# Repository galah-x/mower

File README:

Repository for files to upgrade a Ryobi RM480e ride on battery mower
from its original 4 75AH lead acid batteries
to Lithium Iron Phosphate (LFP) 100AH batteries
With a battery balance facility.

The 12V LFP batteries have internal battery balance, to balance the 4 cells each contains.
This repo is about balancing the 4 12V batteries to each other.

Discussion at https://hackaday.io/project/202788-ryobi-480e-mower-lfp-battery-upgrade-with-balance

Repo signifiant contents:

VMON is the per battery voltage monitor and balance board
vmon/vmn/vmn.ino    arduino code for an esp32
vmon/vmon/vmon.pdf  board schematic
vmon/vmon/gerbers/  board manufacturing info
vmon/vmon           kicad layout directory

IMON is the current monitor from a current shunt
imon/imon.ino       arduino code for an esp32
vmon/imon/imon.pdf  schematic
there is no imon layout, its hacked onto a vmon board as I discovered a design oversight in the
adc on the mco board near the runup phase. Too much of a hurry to mow the lawn to wait for a pcb to be made and shipped.

MCO is the Mower comms controller board. This is where the mower logic runs.
mcomms/mco/mco.ino     and other files in that directory is the arduino source for the mco board
mcomms/mcomms.pdf      board schematic
mcomms/mcomms          kicad layout files
mcomms/mcomms/gerbers  pcb manufacturing files

MMC is the mower charge controller. Really its a display board next to the power supply with a LCD and
rotary encoder. It displays each battery voltage and balance state, charger voltage, charge current, charge state, mower temperature.
mcharger_if/mcharge_if.pdf       schematic
mcharger_if/mcc/mcc.ino          arduino code, together with remainder of the directory
mcharger_if/mcharger_if/         kicad layout dir
mcharger_if/mcharger_if/gerbers  pcb manufacturing information

PSU is a wifi to serial converter used to allow mco to control and monitor the replacement charger, made from a 1200W 60V smps module and a DPM8624 remote programmable power supply.
vichyctl/psu/psu.ino        arduino code for psu
vichyctl/vichyctl.pdf       schematic for board
vichyctl/vichyctl/gerbers/  layout files
vichyctl/vichyctl           kicad layout directory.   Originally a board to permit remote Wifi access to a vichy VC8145 multimeter 

I didn't draw a charger schematic.
Connect the mains to the smps power supply.
Connect the 60V out of the SMPS to the input pins of the DPM8624
Connect the 4 pins on the PSU board (5V, 0V, TX, RX) to the matching 4 control pins on the DPM86224.
Connect the 2 output pins on the DPM8624 to a charger cable likely repurposed from your old charger
in the charger plug, add a wire to connect the middle sense pin to +48V, ie charger positive. 

mower_system_connect is a top level schematic of new stuff in the mower.
mower_system_connect/mower_system_connect.pdf

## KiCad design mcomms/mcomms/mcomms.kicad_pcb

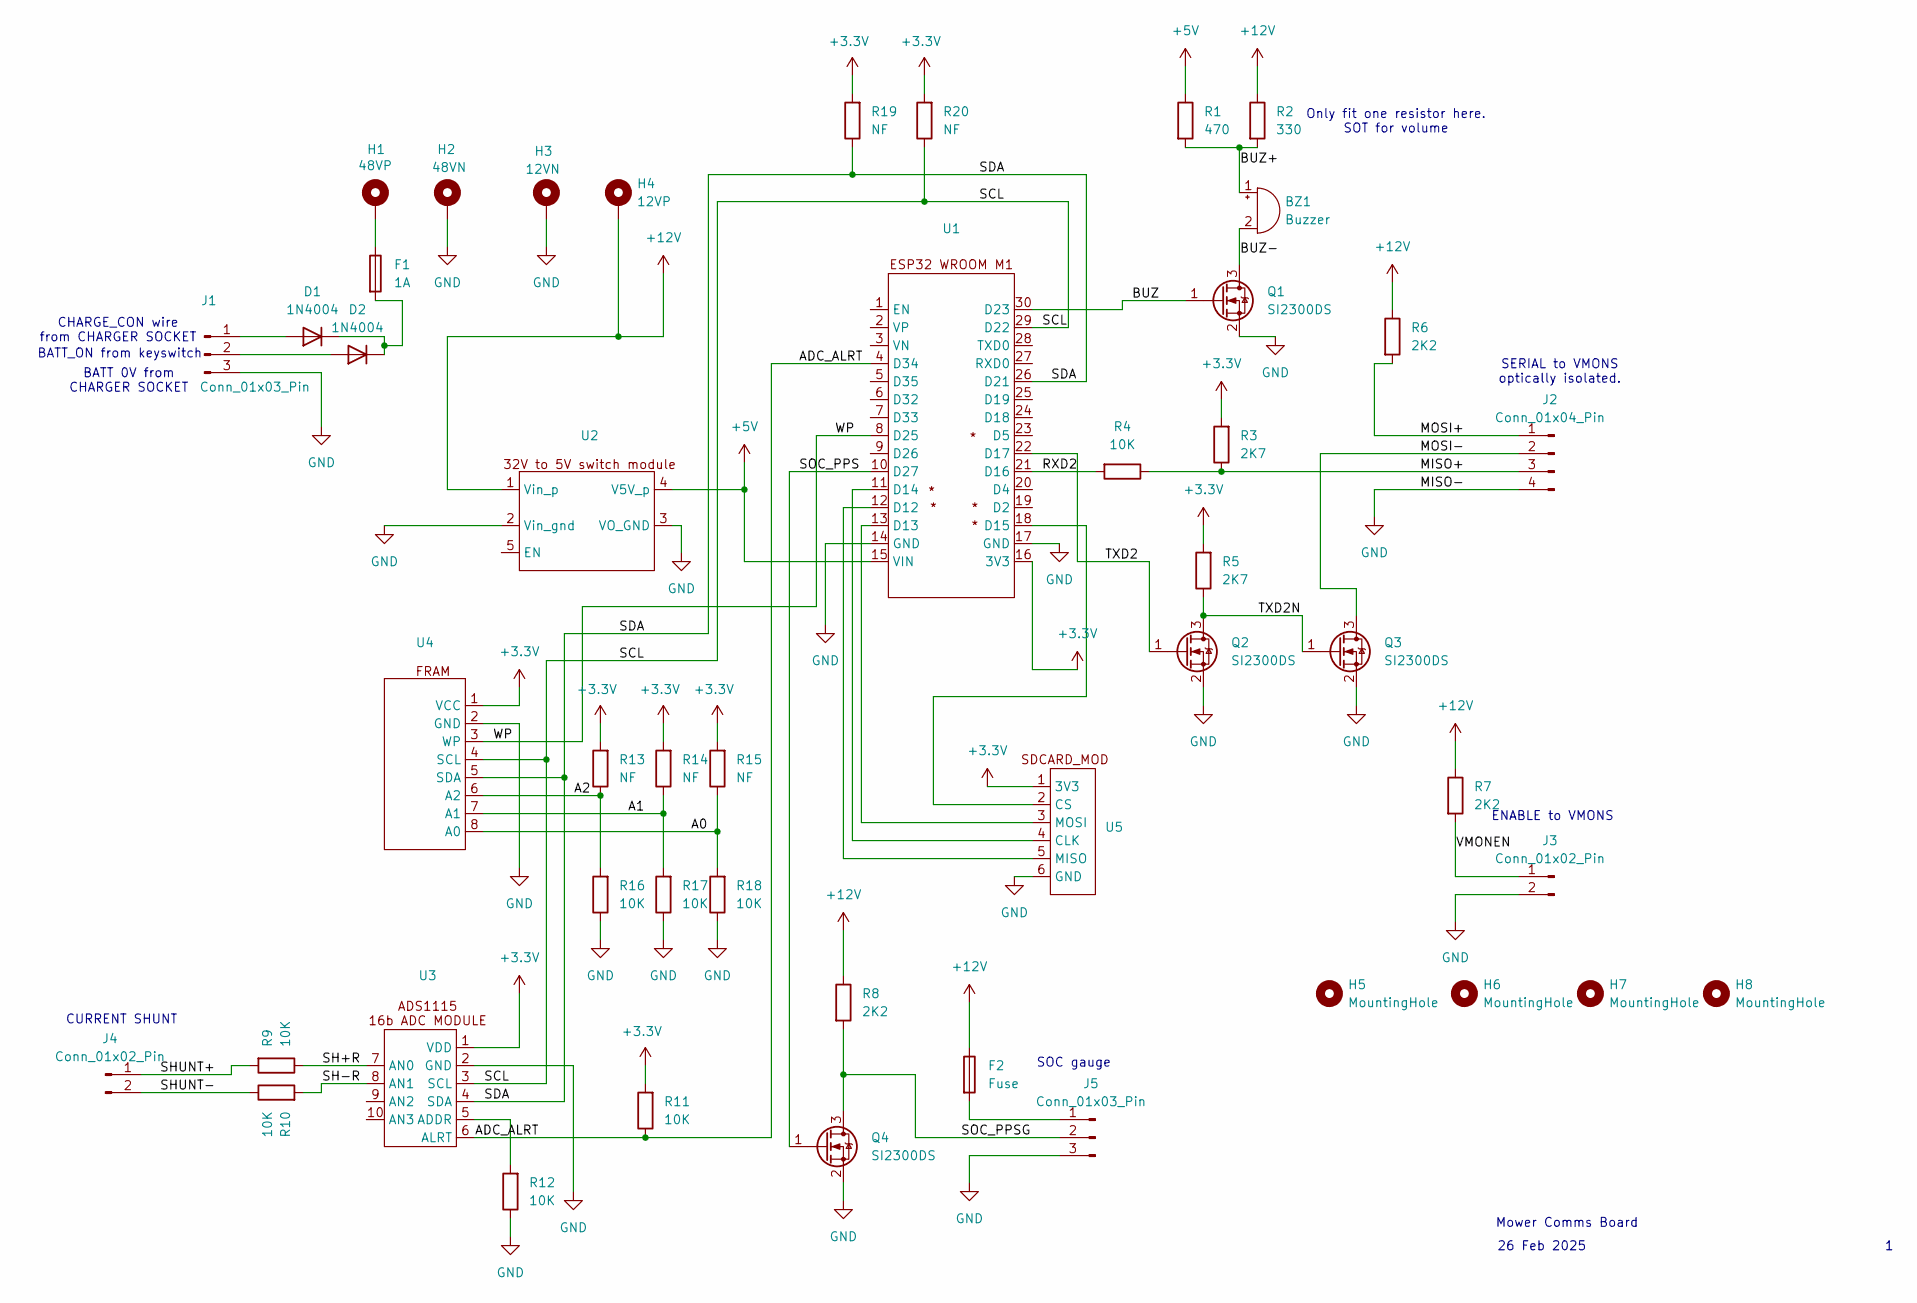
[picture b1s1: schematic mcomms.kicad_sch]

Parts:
BZ1: Buzzer; Buzzer_12x9.5RM7.6
D1, D2: 1N4004; D_A-405_P12.70mm_Horizontal
F1: 1A; Fuse_1206_3216Metric_Pad1.42x1.75mm_HandSolder
F2: Fuse; Fuse_1206_3216Metric_Pad1.42x1.75mm_HandSolder
H1: 48VP; MountingHole_2.2mm_M2_DIN965_Pad_TopBottom
H2: 48VN; MountingHole_2.2mm_M2_DIN965_Pad_TopBottom
H3: 12VN; MountingHole_2.2mm_M2_DIN965_Pad_TopBottom
H4: 12VP; MountingHole_2.2mm_M2_DIN965_Pad_TopBottom
H5, H6, H7, H8: MountingHole; MountingHole_3.2mm_M3_DIN965_Pad
J1, J5: Conn_01x03_Pin; PhoenixContact_MC_1,5_3-G-5.08_1x03_P5.08mm_Horizontal
J2: Conn_01x04_Pin; PhoenixContact_MC_1,5_4-G-5.08_1x04_P5.08mm_Horizontal
J3, J4: Conn_01x02_Pin; PhoenixContact_MC_1,5_2-G-5.08_1x02_P5.08mm_Horizontal
Q1, Q2, Q3, Q4: SI2300DS; SOT-23
R1: 470; R_Axial_DIN0309_L9.0mm_D3.2mm_P12.70mm_Horizontal
R2: 330; R_Axial_DIN0309_L9.0mm_D3.2mm_P12.70mm_Horizontal
R3, R5: 2K7; R_0805_2012Metric_Pad1.20x1.40mm_HandSolder
R4, R9, R10, R11, R12, R16, R17, R18: 10K; R_0805_2012Metric_Pad1.20x1.40mm_HandSolder
R6, R7, R8: 2K2; R_0805_2012Metric_Pad1.20x1.40mm_HandSolder
R13, R14, R15, R19, R20: NF; R_0805_2012Metric_Pad1.20x1.40mm_HandSolder
U1: ESP32_WROOM_M1
U2: switcher_en
U3: R_Array_SIP10
U4: SIP-8_19x3mm_P2.54mm
U5: R_Array_SIP6

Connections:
+3.3V: R3.2, R5.2, R11.2, R13.2, R14.2, R15.2, R19.2, R20.2, U1.16 (3V3), U3.1 (VDD), U4.1 (VCC), U5.1 (3V3)
+5V: R1.1, U1.15 (VIN), U2.4 (V5V_p)
+12V: F2.1, H4.1, R2.1, R6.1, R7.1, R8.1, U2.1 (Vin_p)
/A0: R15.1, R18.2, U4.8 (A0)
/A1: R14.1, R17.2, U4.7 (A1)
/A2: R13.1, R16.2, U4.6 (A2)
/ADC_ALRT: R11.1, U1.4 (D34), U3.6 (ALRT)
/BUZ: Q1.1 (G), U1.30 (D23)
/BUZ+: BZ1.1 (+), R1.2, R2.2
/BUZ-: BZ1.2 (-), Q1.3 (D)
/MISO+: J2.3, R3.1, R4.1
/MOSI+: J2.1, R6.2
/MOSI-: J2.2, Q3.3 (D)
/RXD2: R4.2, U1.21 (D16)
/SCL: R20.1, U1.29 (D22), U3.3 (SCL), U4.4 (SCL)
/SDA: R19.1, U1.26 (D21), U3.4 (SDA), U4.5 (SDA)
/SH+R: R9.1, U3.7 (AN0)
/SH-R: R10.2, U3.8 (AN1)
/SHUNT+: J4.1, R9.2
/SHUNT-: J4.2, R10.1
/SOC_PPS: Q4.1 (G), U1.10 (D27)
/SOC_PPSG: J5.2, Q4.3 (D), R8.2
/TXD2: Q2.1 (G), U1.22 (D17)
/TXD2N: Q2.3 (D), Q3.1 (G), R5.1
/VMONEN: J3.1, R7.2
/WP: U1.8 (D25), U4.3 (WP)
GND: H2.1, H3.1, J1.3, J2.4, J3.2, J5.3, Q1.2 (S), Q2.2 (S), Q3.2 (S), Q4.2 (S), R12.1, R16.1, R17.1, R18.1, U1.14 (GND), U1.17 (GND), U2.2 (Vin_gnd), U2.3 (VO_GND), U3.2 (GND), U4.2 (GND), U5.6 (GND)
unnamed: D1.2 (A), J1.1
unnamed: D1.1 (K), D2.1 (K), F1.2
unnamed: D2.2 (A), J1.2
unnamed: F1.1, H1.1
unnamed: F2.2, J5.1
unnamed: U1.12 (D12), U5.5 (MISO)
unnamed: U1.13 (D13), U5.3 (MOSI)
unnamed: U1.11 (D14), U5.4 (CLK)
unnamed: U1.18 (D15), U5.2 (CS)
unnamed: R12.2, U3.5 (ADDR)

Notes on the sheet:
SERIAL to VMONS optically isolated.
CHARGE_CON wire from CHARGER SOCKET
CURRENT SHUNT
ENABLE to VMONS
BATT_ON from keyswitch
Mower Comms Board
BATT 0V from CHARGER SOCKET
26 Feb 2025
SOC gauge
Only fit one resistor here. SOT for volume

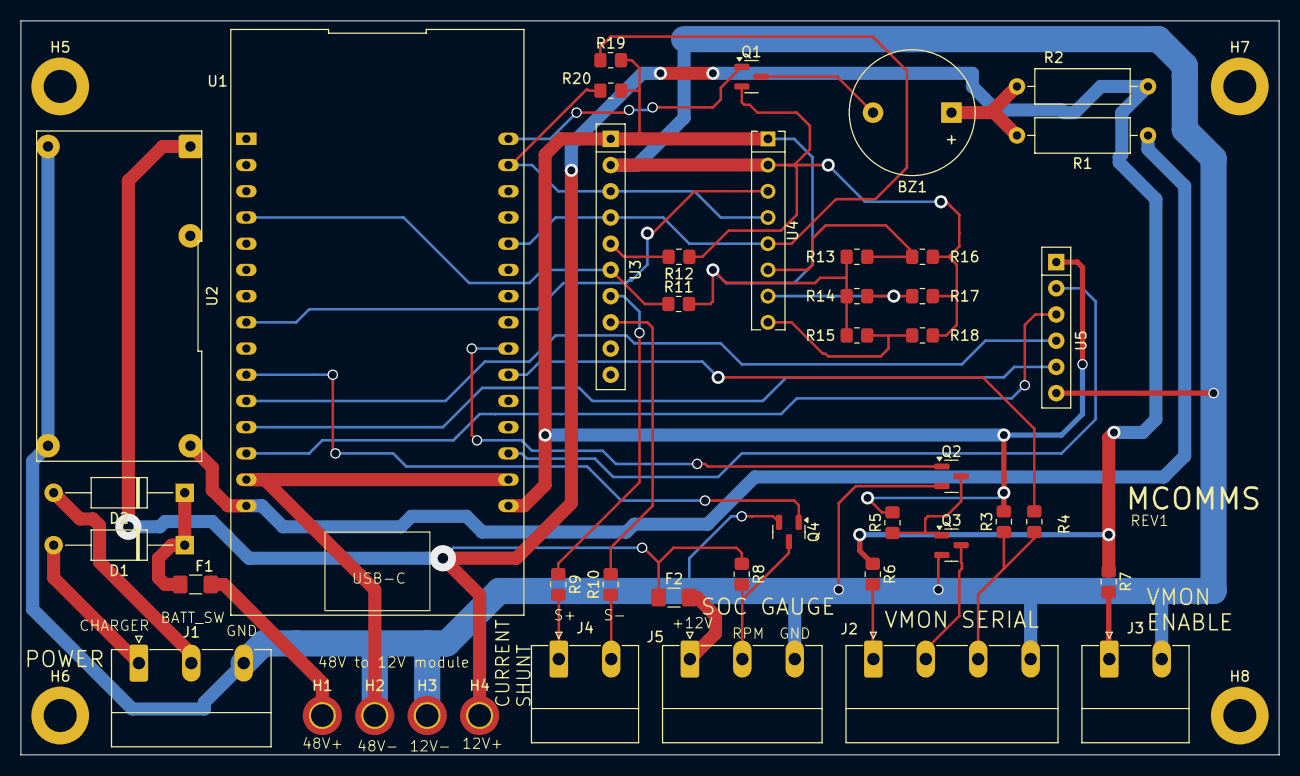
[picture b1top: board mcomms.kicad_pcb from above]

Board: 2 copper layers, 121.9 x 71.1 mm, 47 parts (0 on the bottom side), 37 nets.

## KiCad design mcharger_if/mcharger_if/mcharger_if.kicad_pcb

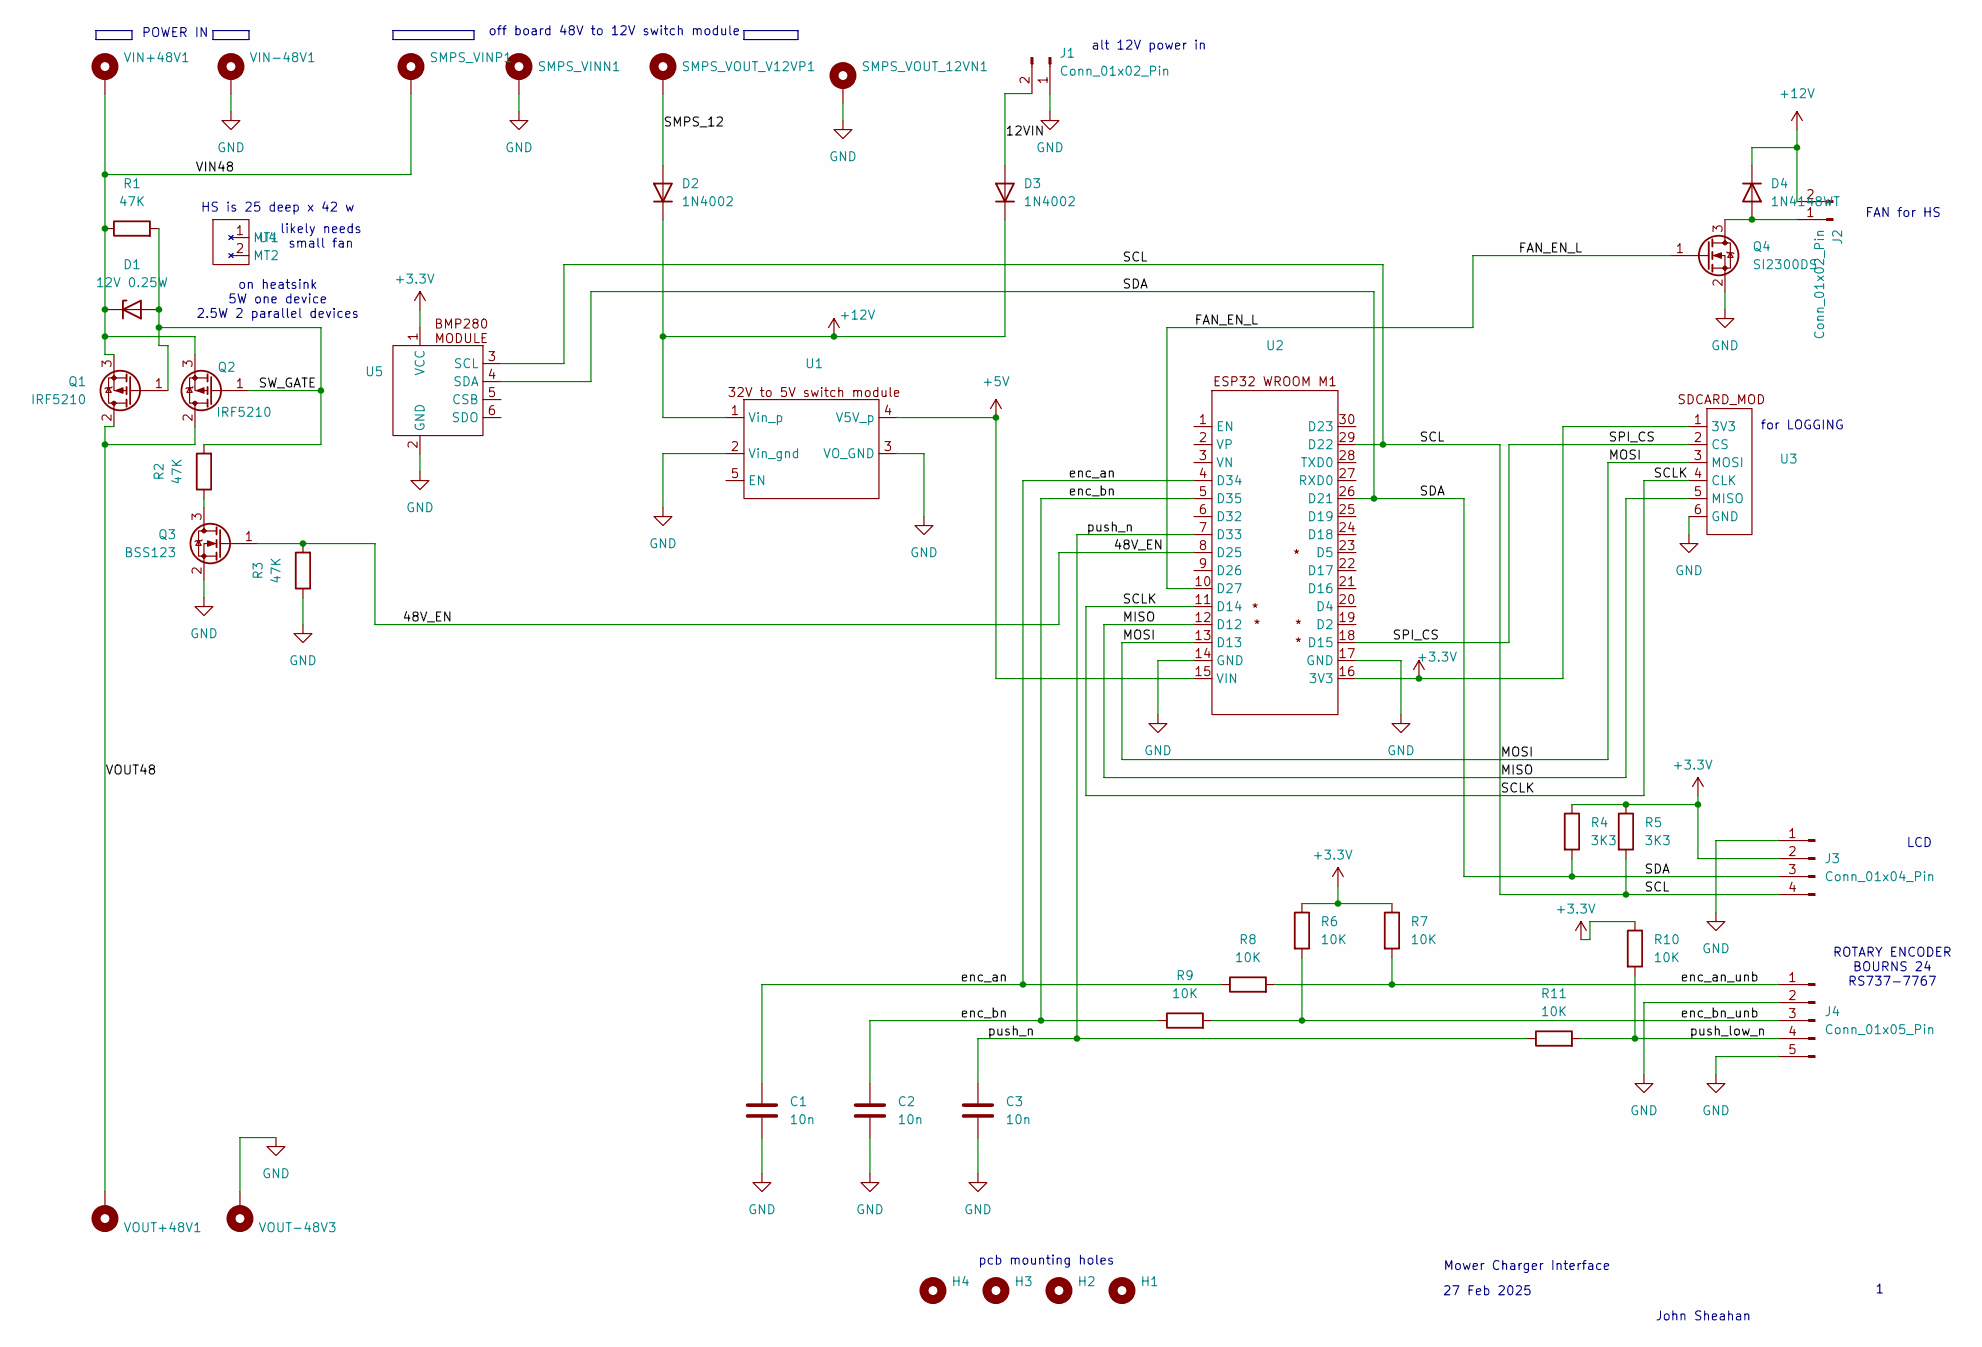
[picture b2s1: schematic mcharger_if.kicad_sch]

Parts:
C1, C2, C3: 10n; C_0603_1608Metric_Pad1.08x0.95mm_HandSolder
D1: 12V 0.25W; D_0805_2012Metric_Pad1.15x1.40mm_HandSolder
D2, D3: 1N4002; D_DO-41_SOD81_P10.16mm_Horizontal
D4: 1N4148WT; D_SOD-523
H1, H2, H3, H4: MountingHole; MountingHole_3.2mm_M3_DIN965
J1, J2: Conn_01x02_Pin; PhoenixContact_MC_1,5_2-G-5.08_1x02_P5.08mm_Horizontal
J3: Conn_01x04_Pin; JST_XH_B4B-XH-AM_1x04_P2.50mm_Vertical
J4: Conn_01x05_Pin; JST_XH_B5B-XH-A_1x05_P2.50mm_Vertical
Q1, Q2: IRF5210; TO-220-3_Vertical
Q3: BSS123; SOT-23
Q4: SI2300DS; SOT-23
R1, R2, R3: 47K; R_0805_2012Metric_Pad1.20x1.40mm_HandSolder
R4, R5: 3K3; R_0805_2012Metric_Pad1.20x1.40mm_HandSolder
R6, R7, R8, R9, R10, R11: 10K; R_0805_2012Metric_Pad1.20x1.40mm_HandSolder
SMPS_VINN1: MountingHole_Pad; MountingHole_2.2mm_M2_DIN965_Pad_TopBottom
SMPS_VINP1: MountingHole_Pad; MountingHole_2.2mm_M2_DIN965_Pad_TopBottom
SMPS_VOUT_12VN1: MountingHole_Pad; MountingHole_2.2mm_M2_DIN965_Pad_TopBottom
SMPS_VOUT_V12VP1: MountingHole_Pad; MountingHole_2.2mm_M2_DIN965_Pad_TopBottom
U1: switcher_en
U2: ESP32_WROOM_M1
U3, U5: R_Array_SIP6
U4: TO220_m1
VIN+48V1: MountingHole_Pad; MountingHole_3.2mm_M3_DIN965_Pad_TopBottom
VIN-48V1: MountingHole_Pad; MountingHole_3.2mm_M3_DIN965_Pad_TopBottom
VOUT+48V1: MountingHole_Pad; MountingHole_3.2mm_M3_DIN965_Pad_TopBottom
VOUT-48V3: MountingHole_Pad; MountingHole_3.2mm_M3_DIN965_Pad_TopBottom

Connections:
+3.3V: J3.2, R4.1, R5.1, R6.1, R7.1, R10.1, U2.16 (3V3), U3.1 (3V3), U5.1 (VCC)
+5V: U1.4 (V5V_p), U2.15 (VIN)
+12V: D2.1 (K), D3.1 (K), D4.1 (K), J2.2, U1.1 (Vin_p)
/12VIN: D3.2 (A), J1.2
/48V_EN: Q3.1 (G), R3.2, U2.8 (D25)
/FAN_EN_L: Q4.1 (G), U2.10 (D27)
/SDA: J3.3, R4.2, U2.26 (D21), U5.4 (SDA)
/SMPS_12: D2.2 (A), SMPS_VOUT_V12VP1.1
/SPI_CS: U2.18 (D15), U3.2 (CS)
/SW_GATE: D1.2 (A), Q1.1 (G), Q2.1 (G), R1.2, R2.2
/VIN48: D1.1 (K), Q1.3 (S), Q2.3 (S), R1.1, SMPS_VINP1.1, VIN+48V1.1
/VOUT48: Q1.2 (D), Q2.2 (D), VOUT+48V1.1
/enc_an: C1.1, R8.1, U2.4 (D34)
/enc_an_unb: J4.1, R7.2, R8.2
/enc_bn: C2.1, R9.1, U2.5 (D35)
/enc_bn_unb: J4.3, R6.2, R9.2
/push_low_n: J4.4, R10.2, R11.2
/push_n: C3.1, R11.1, U2.7 (D33)
GND: C1.2, C2.2, C3.2, J1.1, J3.1, J4.2, J4.5, Q3.2 (S), Q4.2 (S), R3.1, SMPS_VINN1.1, SMPS_VOUT_12VN1.1, U1.2 (Vin_gnd), U1.3 (VO_GND), U2.14 (GND), U2.17 (GND), U3.6 (GND), U5.2 (GND), VIN-48V1.1, VOUT-48V3.1
unnamed: D4.2 (A), J2.1, Q4.3 (D)
unnamed: Q3.3 (D), R2.1

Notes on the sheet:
likely needs small fan
for LOGGING
POWER IN
FAN for HS
27 Feb 2025
John Sheahan
Mower Charger Interface
HS is 25 deep x 42 w
pcb mounting holes
off board 48V to 12V switch module
LCD
on heatsink 5W one device 2.5W 2 parallel devices
ROTARY ENCODER BOURNS 24 RS737-7767
alt 12V power in

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
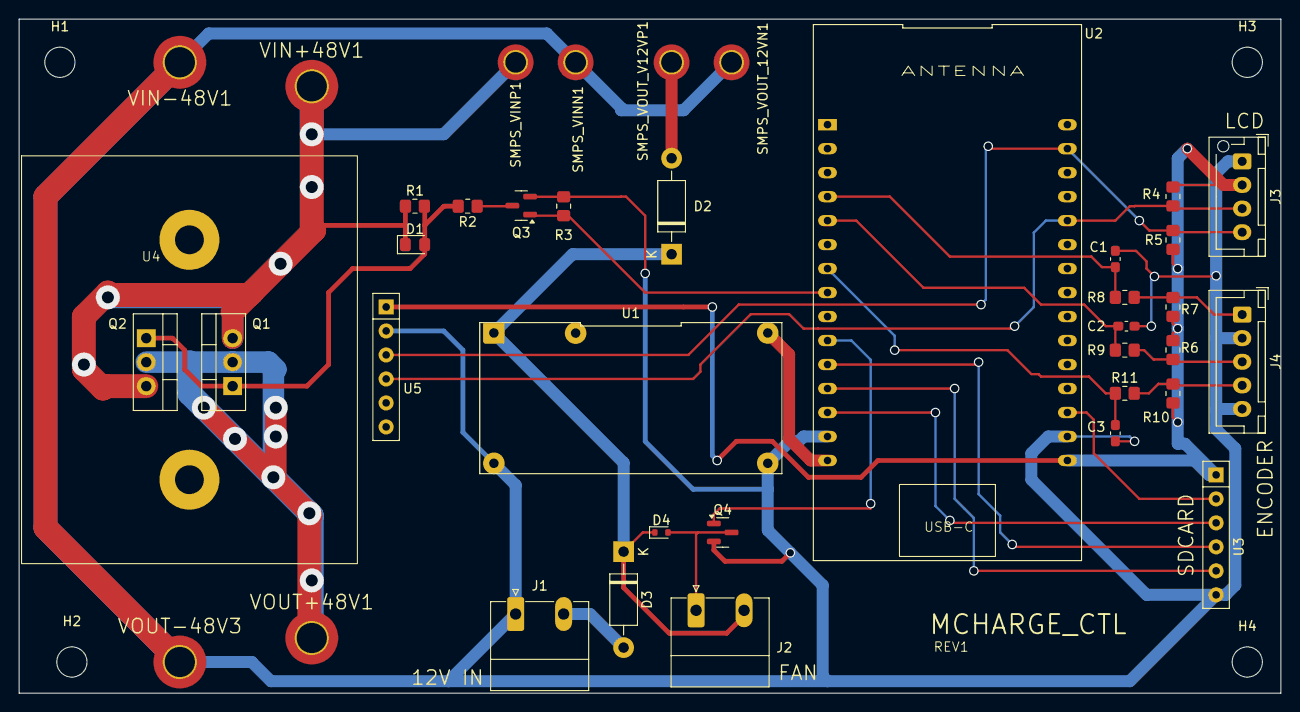
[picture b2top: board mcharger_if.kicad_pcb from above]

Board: 2 copper layers, 133.6 x 71.4 mm, 43 parts (0 on the bottom side), 25 nets.

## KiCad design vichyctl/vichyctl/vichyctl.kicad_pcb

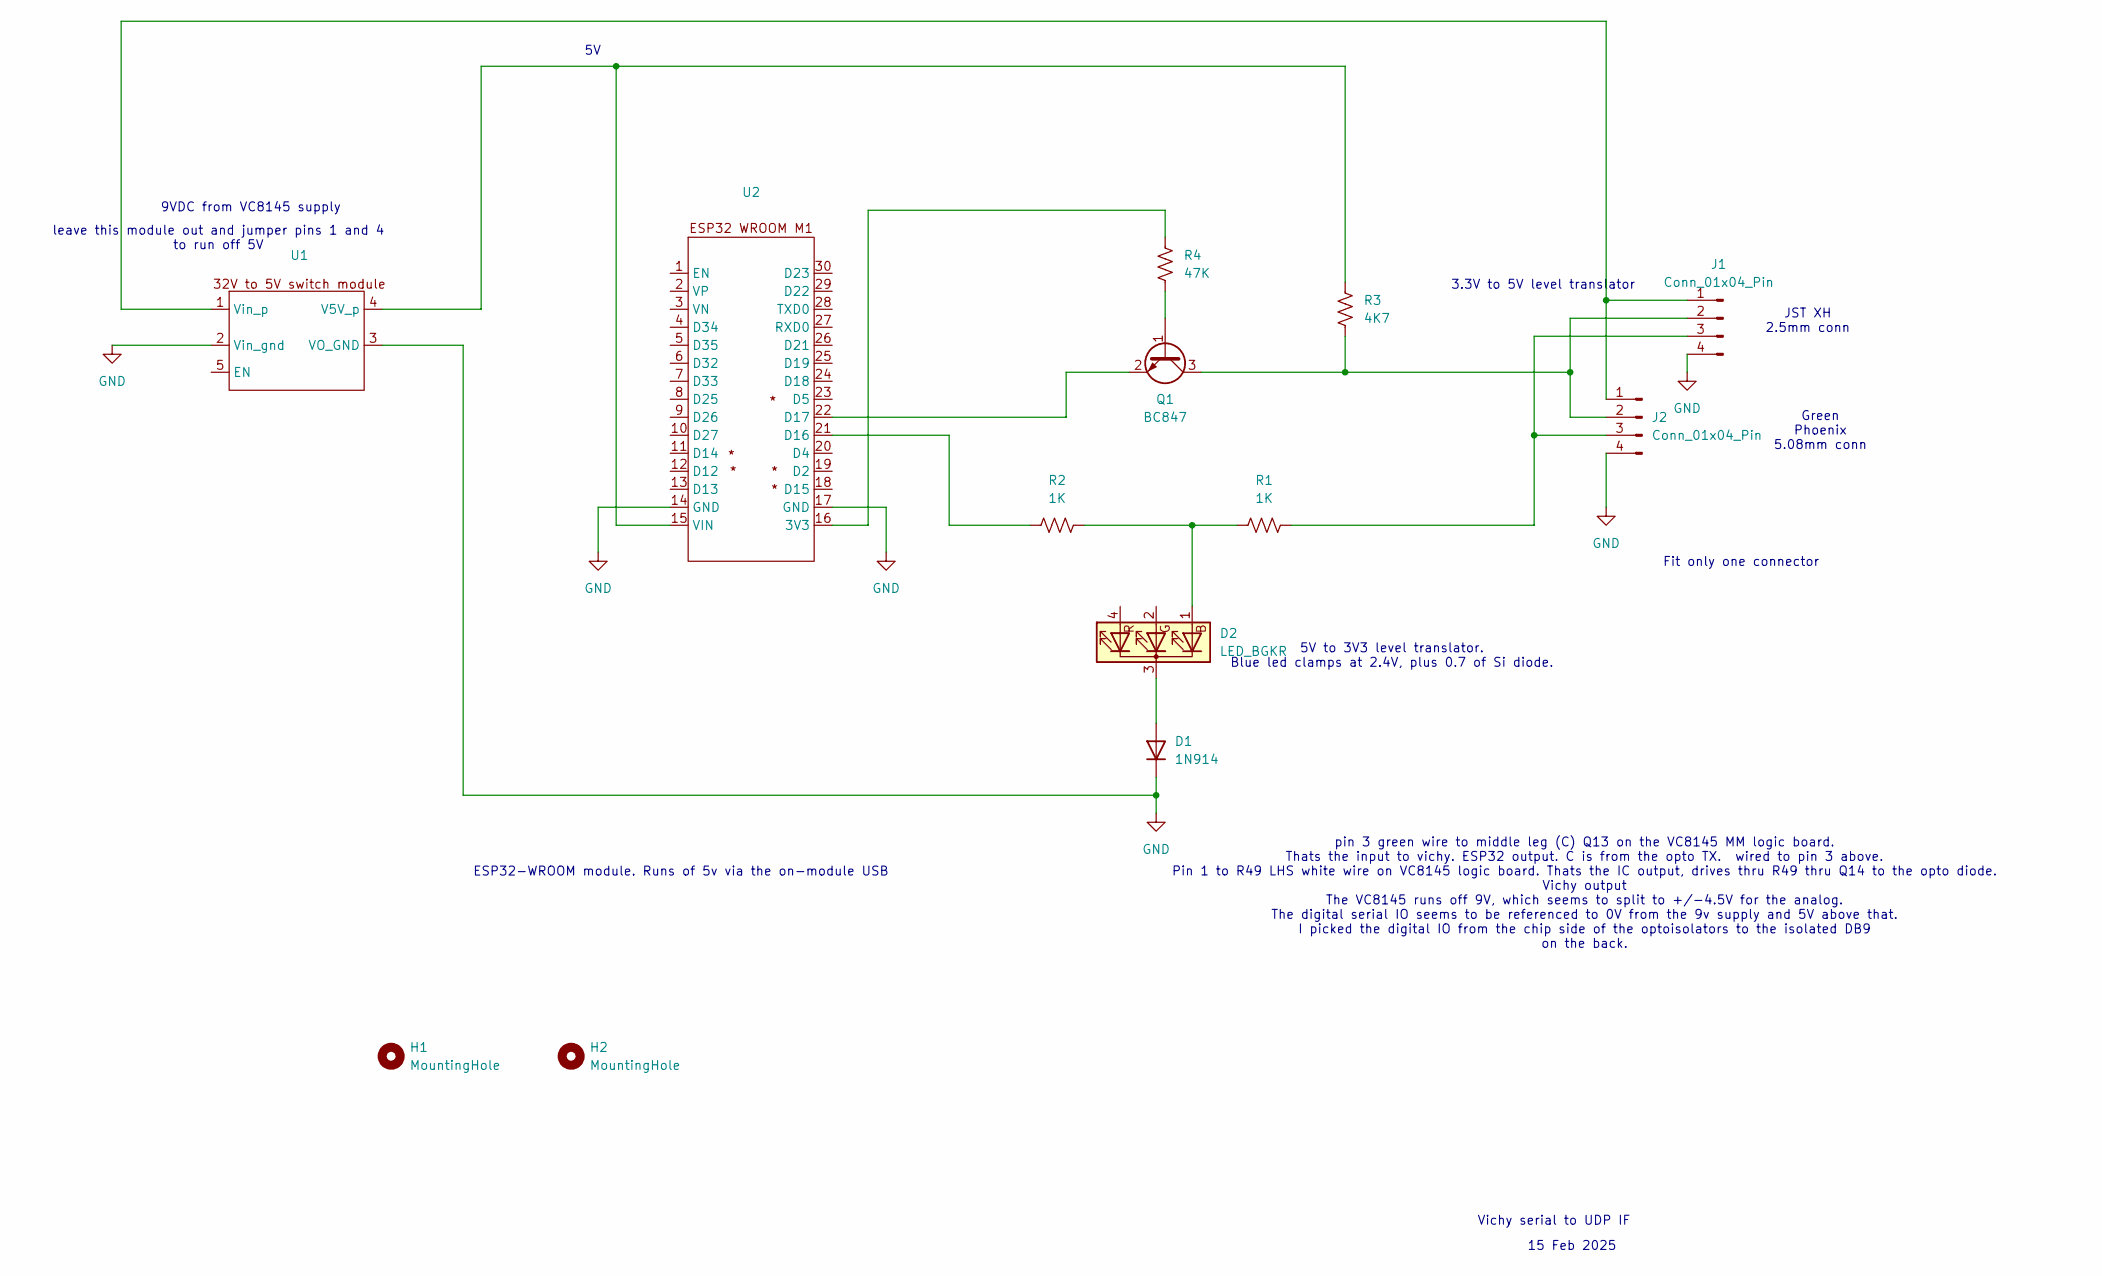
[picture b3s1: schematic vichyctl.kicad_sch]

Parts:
D1: 1N914; D_0603_1608Metric_Pad1.05x0.95mm_HandSolder
D2: LED_BGKR; LED_D5.0mm-4_RGB_Wide_Pins
H1, H2: MountingHole; MountingHole_3.2mm_M3_ISO7380
J1: Conn_01x04_Pin; JST_XH_B4B-XH-A_1x04_P2.50mm_Vertical
J2: Conn_01x04_Pin; PhoenixContact_MC_1,5_4-G-5.08_1x04_P5.08mm_Horizontal
Q1: BC847; SOT-23
R1, R2: 1K; R_0805_2012Metric_Pad1.20x1.40mm_HandSolder
R3: 4K7; R_0805_2012Metric_Pad1.20x1.40mm_HandSolder
R4: 47K; R_0805_2012Metric_Pad1.20x1.40mm_HandSolder
U1: switcher_en
U2: ESP32_WROOM_M1

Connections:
GND: D1.1 (K), J1.4, J2.4, U1.2 (Vin_gnd), U1.3 (VO_GND), U2.14 (GND), U2.17 (GND)
unnamed: D1.2 (A), D2.3 (K)
unnamed: D2.1 (BA), R1.1, R2.2
unnamed: J1.1, J2.1, U1.1 (Vin_p)
unnamed: J1.2, J2.2, Q1.3 (C), R3.2
unnamed: J1.3, J2.3, R1.2
unnamed: Q1.1 (B), R4.1
unnamed: Q1.2 (E), U2.22 (D17)
unnamed: R4.2, U2.16 (3V3)
unnamed: R2.1, U2.21 (D16)
unnamed: R3.1, U1.4 (V5V_p), U2.15 (VIN)

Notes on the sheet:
Fit only one connector
5V to 3V3 level translator. Blue led clamps at 2.4V, plus 0.7 of Si diode.
ESP32-WROOM module. Runs of 5v via the on-module USB
9VDC from VC8145 supply
leave this module out and jumper pins 1 and 4 to run off 5V
JST XH 2.5mm conn
Green Phoenix 5.08mm conn
15 Feb 2025
3.3V to 5V level translator
pin 3 green wire to middle leg (C) Q13 on the VC8145 MM logic board. Thats the input to vichy. ESP32 output. C is from the opto TX. wired to pin 3 above. Pin 1 to R49 LHS white wire on VC8145 logic board. Thats the IC output, drives thru R49 thru Q14 to the opto diode. Vichy output The VC8145 runs 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
Vichy serial to UDP IF

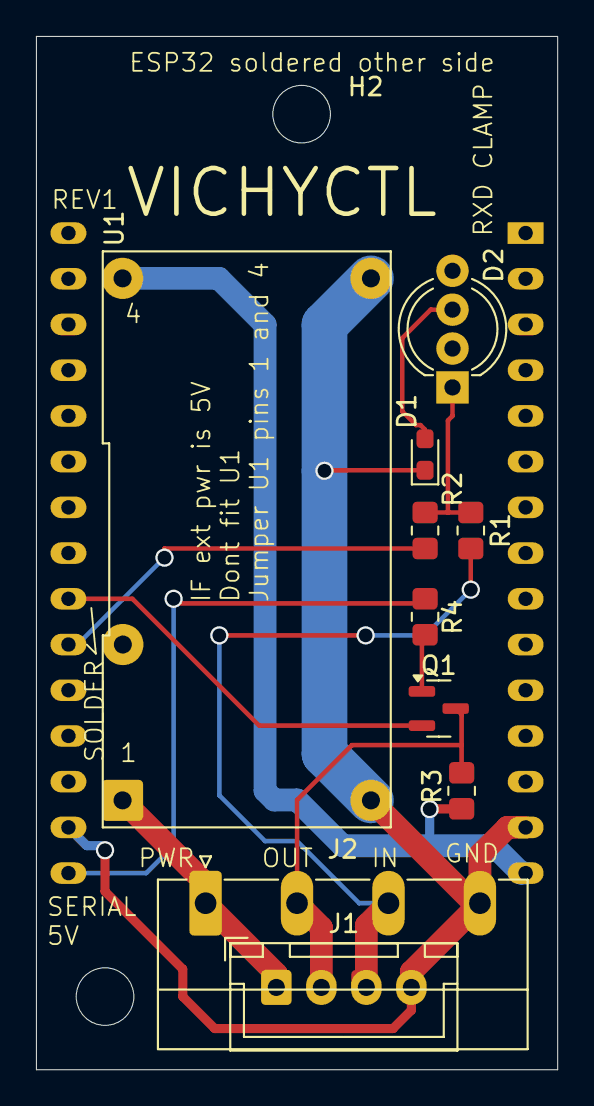
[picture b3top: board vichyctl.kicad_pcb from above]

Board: 2 copper layers, 29.0 x 57.4 mm, 13 parts (1 on the bottom side), 11 nets.

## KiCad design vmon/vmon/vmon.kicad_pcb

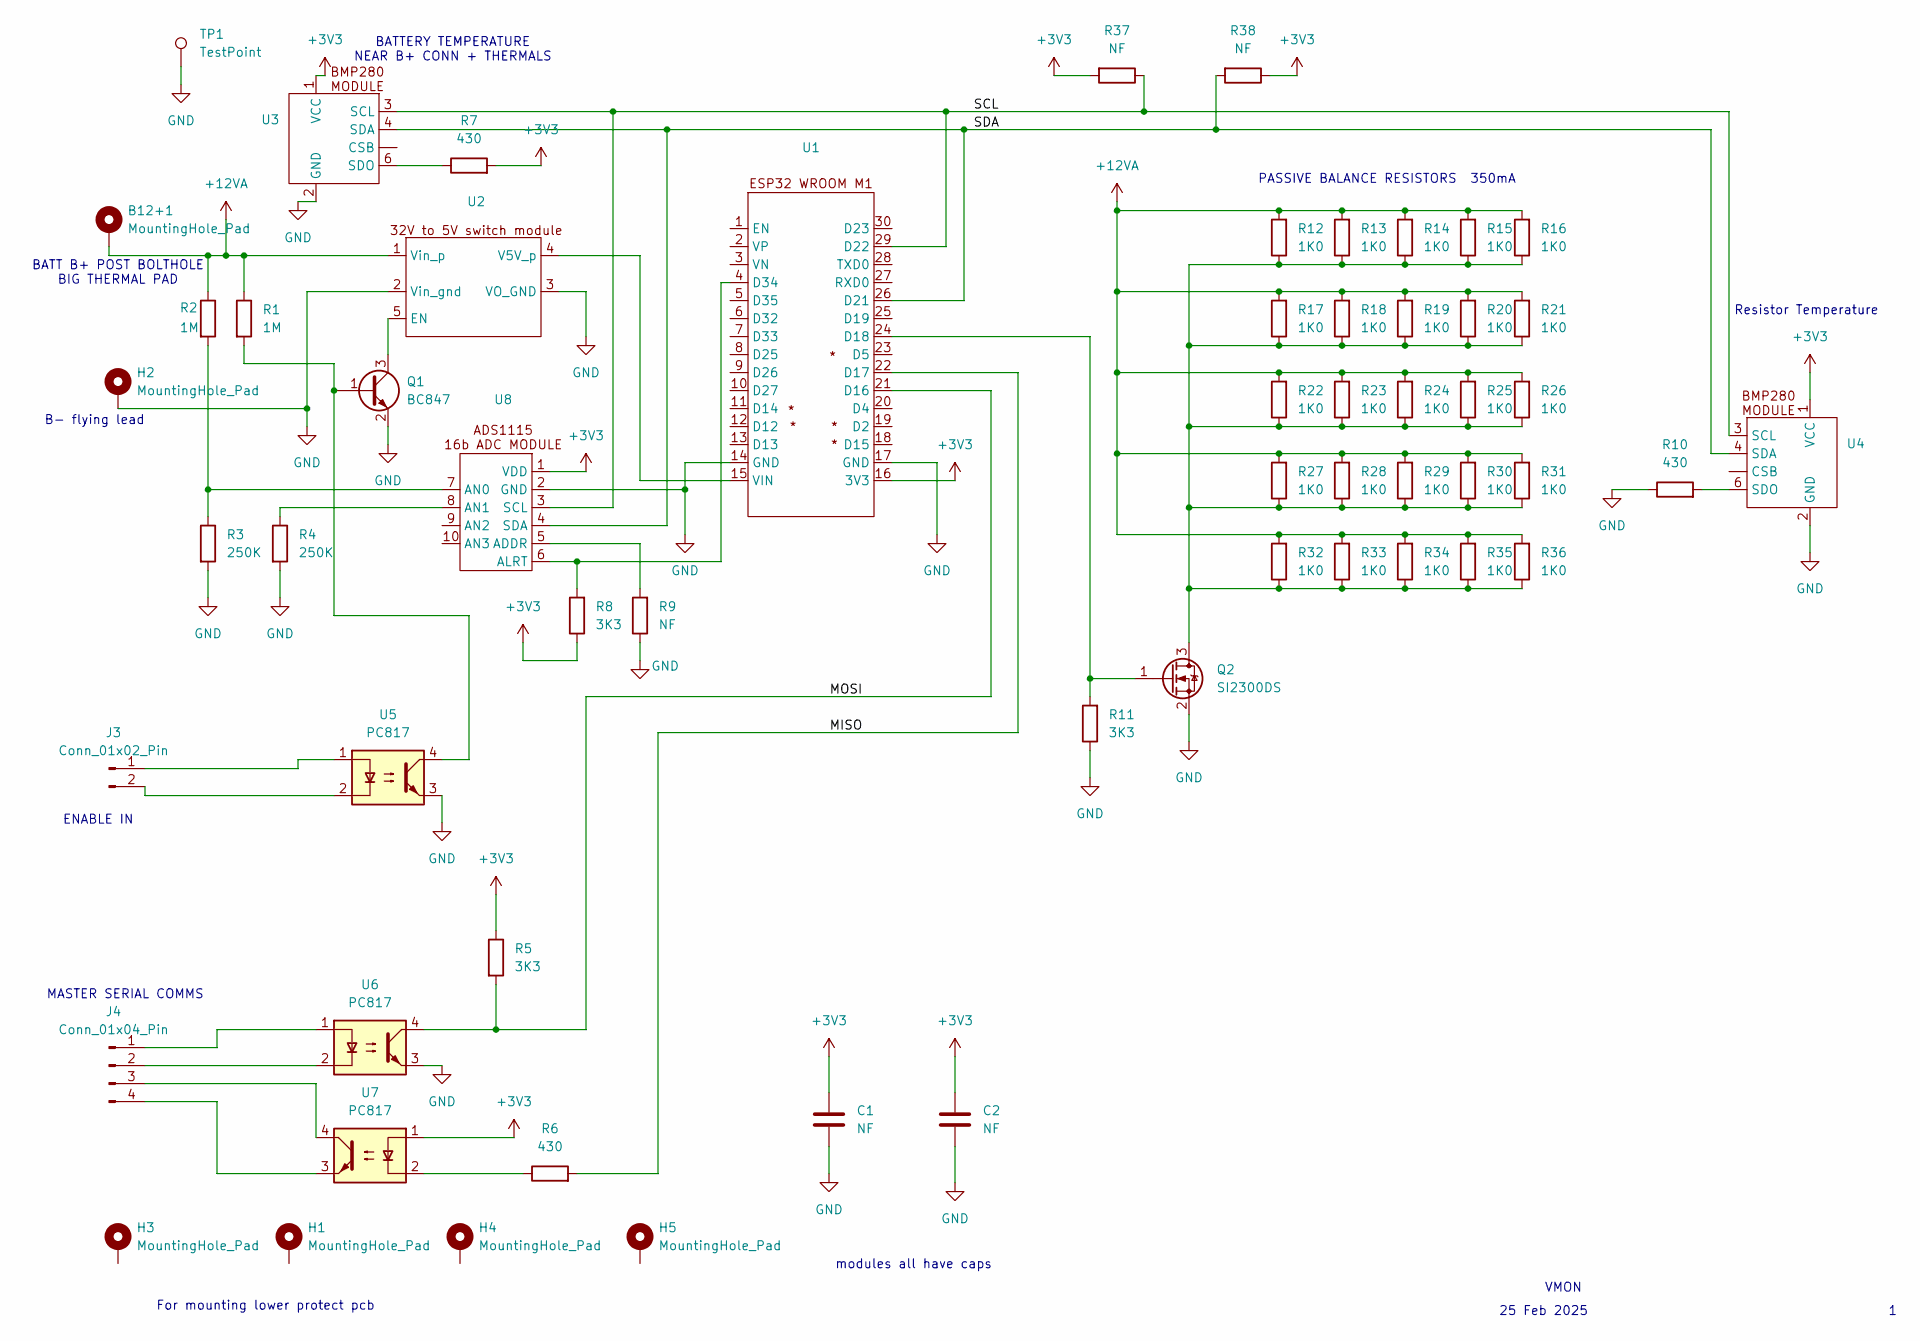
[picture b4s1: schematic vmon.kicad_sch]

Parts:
B12+1: MountingHole_Pad; MountingHole_8.4mm_M8_Pad_TopBottom
C1: NF; C_1210_3225Metric_Pad1.33x2.70mm_HandSolder
C2: NF; C_0603_1608Metric
H1, H3, H4, H5: MountingHole_Pad; MountingHole_3.2mm_M3_DIN965_Pad_TopBottom
H2: MountingHole_Pad; MountingHole_2.5mm_Pad_TopBottom
J3: Conn_01x02_Pin; PhoenixContact_MC_1,5_2-G-5.08_1x02_P5.08mm_Horizontal
J4: Conn_01x04_Pin; PhoenixContact_MC_1,5_4-G-5.08_1x04_P5.08mm_Horizontal
Q1: BC847; SOT-23
Q2: SI2300DS; SOT-23
R1, R2: 1M; R_0805_2012Metric_Pad1.20x1.40mm_HandSolder
R3, R4: 250K; R_0805_2012Metric_Pad1.20x1.40mm_HandSolder
R5, R8, R11: 3K3; R_0805_2012Metric_Pad1.20x1.40mm_HandSolder
R6, R7, R10: 430; R_0805_2012Metric_Pad1.20x1.40mm_HandSolder
R9, R37, R38: NF; R_0805_2012Metric_Pad1.20x1.40mm_HandSolder
R12, R13, R14, R15, R16, R17, R18, R19, R20, R21, R22, R23, R24, R25, R26, R27, R28, R29, R30, R31, R32, R33, R34, R35, R36: 1K0; R_2512_6332Metric_Pad1.40x3.35mm_HandSolder
TP1: TestPoint; Pin_D0.9mm_L10.0mm_W2.4mm_FlatFork
U1: ESP32_WROOM_M1
U2: switcher_en
U3, U4: R_Array_SIP6
U5, U6, U7: PC817; DIP-4_W7.62mm
U8: R_Array_SIP10

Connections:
+3V3: C1.1, C2.1, R5.1, R7.2, R8.1, R37.2, R38.1, U1.16 (3V3), U3.1 (VCC), U4.1 (VCC), U7.1, U8.1 (VDD)
+12VA: B12+1.1, R1.1, R2.1, R12.2, R13.2, R14.2, R15.2, R16.2, R17.2, R18.2, R19.2, R20.2, R21.2, R22.2, R23.2, R24.2, R25.2, R26.2, R27.2, R28.2, R29.2, R30.2, R31.2, R32.2, R33.2, R34.2, R35.2, R36.2, U2.1 (Vin_p)
/MISO: R6.2, U1.22 (D17)
/MOSI: R5.2, U1.21 (D16), U6.4
/SCL: R37.1, U1.29 (D22), U3.3 (SCL), U4.3 (SCL), U8.3 (SCL)
/SDA: R38.2, U1.26 (D21), U3.4 (SDA), U4.4 (SDA), U8.4 (SDA)
GND: C1.2, C2.2, H2.1, Q1.2 (E), Q2.2 (S), R3.2, R4.2, R9.1, R10.1, R11.1, TP1.1, U1.14 (GND), U1.17 (GND), U2.2 (Vin_gnd), U2.3 (VO_GND), U3.2 (GND), U4.2 (GND), U5.3, U6.3, U8.2 (GND)
unnamed: J3.1, U5.1
unnamed: J3.2, U5.2
unnamed: J4.1, U6.1
unnamed: J4.2, U6.2
unnamed: J4.3, U7.4
unnamed: J4.4, U7.3
unnamed: Q1.1 (B), R1.2, U5.4
unnamed: Q1.3 (C), U2.5 (EN)
unnamed: Q2.3 (D), R12.1, R13.1, R14.1, R15.1, R16.1, R17.1, R18.1, R19.1, R20.1, R21.1, R22.1, R23.1, R24.1, R25.1, R26.1, R27.1, R28.1, R29.1, R30.1, R31.1, R32.1, R33.1, R34.1, R35.1, R36.1
unnamed: Q2.1 (G), R11.2, U1.24 (D18)
unnamed: R6.1, U7.2
unnamed: R8.2, U1.4 (D34), U8.6 (ALRT)
unnamed: U1.15 (VIN), U2.4 (V5V_p)
unnamed: R7.1, U3.6 (SDO)
unnamed: R10.2, U4.6 (SDO)
unnamed: R9.2, U8.5 (ADDR)
unnamed: R2.2, R3.1, U8.7 (AN0)
unnamed: R4.1, U8.8 (AN1)

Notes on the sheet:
VMON
25 Feb 2025
BATTERY TEMPERATURE NEAR B+ CONN + THERMALS
For mounting lower protect pcb
B- flying lead
MASTER SERIAL COMMS
PASSIVE BALANCE RESISTORS 350mA
ENABLE IN
BATT B+ POST BOLTHOLE BIG THERMAL PAD
modules all have caps
Resistor Temperature

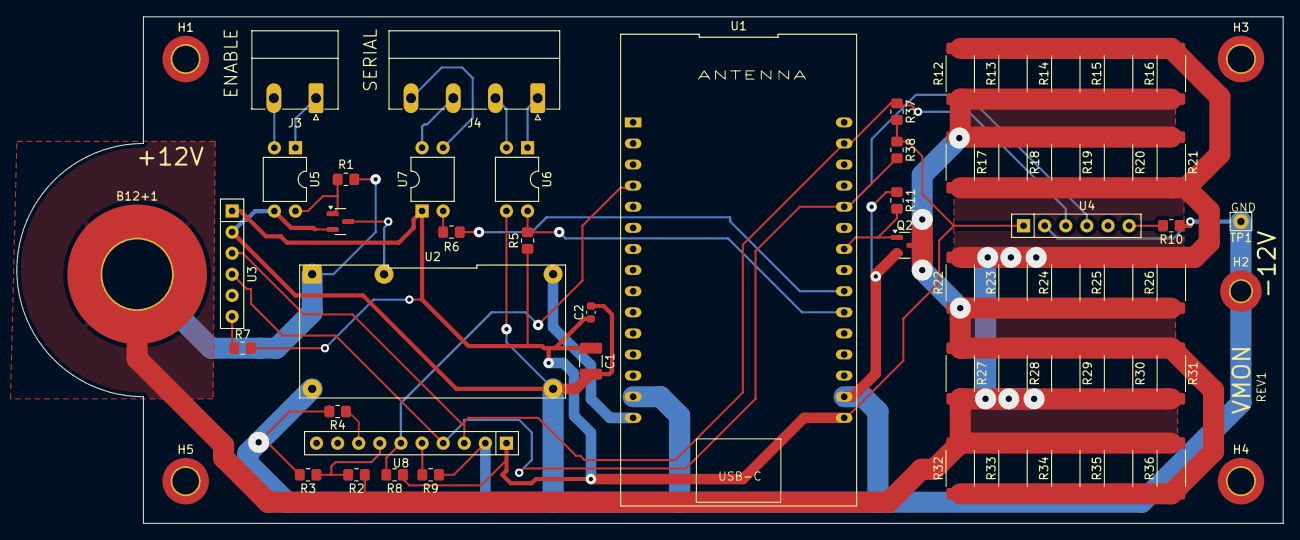
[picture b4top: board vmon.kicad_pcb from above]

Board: 2 copper layers, 152.4 x 61.0 mm, 59 parts (0 on the bottom side), 25 nets.

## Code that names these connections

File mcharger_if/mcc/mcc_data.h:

//    -*- Mode: c++     -*-
// emacs automagically updates the timestamp field on save
// my $ver =  'mcc_data.h  Time-stamp: "2026-03-26 18:02:35 john";

#include <Preferences.h>  // the NV memory interface
#include <Wire.h>
#include <Adafruit_Sensor.h>
#include <Adafruit_BMP280.h>
#include "ESP32Time.h"   // must be V2.x or newer. V1.04 takes 5s to return a time string. breaks logging 
#include <stdio.h>
#include <esp_now.h>
#include <WiFi.h>
#include <esp_wifi.h>
#include <hd44780.h>   // lcd library
#include <hd44780ioClass/hd44780_I2Cexp.h> // include i/o class header
#include <RotaryEncoder.h>
#include "FS.h"            // filesystem for sd logging
#include "SD.h"            // SD apparently uses ram more effectively than SDFat
#include "SPI.h"           // SPI access to sd card
#include <WiFiUdp.h>


// for preferences
#define RW_MODE false
#define RO_MODE true


// serial is used for debug and for programming NVM
const uint8_t longest_record = 24;  //   worst is display comand WD1=12345678901234567890
const uint8_t record_size = longest_record + 2;    //  char char = nnnnn \n
uint8_t serial_buf[record_size];
uint8_t serial_buf_pointer;

// this is used to buffer up the SD logging
const uint16_t sdblksize = 4096; // blksize is always 512, cluster size usually 4k. 
uint8_t sdbuf[sdblksize];
uint16_t sdbuf_ptr;

uint8_t baseMac[6];         // my own mac address
const  uint8_t msgbuflen= 128;  // for wifi transfers
uint8_t return_buf[msgbuflen]; // for responses

const char * version = "MCC 26 Mar 2026 Reva";


Preferences mccPrefs;  // NVM structure
// these will be initialized from the NV memory

int     fan_on_temp;
int     fan_off_temp;
bool    logging;
bool    writing_to_log;
uint8_t psu_mac[6];
uint8_t mco_mac[6];

// these are for WiFi access when moving the logfile around   
const uint8_t ssid_len = 40;
char   ssid[ssid_len];
char   password[ssid_len];

// this inhibits wifi updates writing to the display while the UI is being used.
// Doesn't stop logging of 'lost' screen data.
bool UI_owns_display;

typedef struct struct_message {
  uint8_t message[msgbuflen];
} struct_message;

// create the wifi message struct
struct_message message_data;

esp_now_peer_info_t peerInfo;


/* IOs  definitions */
const uint8_t enc_an_pin  = 34;    // rotary encoder a
const uint8_t enc_bn_pin  = 35;    // rotary encoder b
const uint8_t enc_pushn_pin = 33;    // rotary encoder pushbutton
const uint8_t spi_sclk_pin = 14;
const uint8_t spi_cs_pin   = 15;  // sdcard
const uint8_t spi_mosi_pin = 13;
const uint8_t spi_miso_pin = 12;  
const uint8_t power48V_en_pin = 25;    // turn on 48V to mower
const uint8_t fan_en_pin = 27;    // turn on fan 
const uint8_t sda_pin   = 21;    // fan3
const uint8_t scl_pin   = 22;    // fan3

// I2C addresses 
const uint8_t hs_temperature_addr = 0x76;
const uint8_t display_addr = 0x27;

Adafruit_BMP280 tsense;    // I2C connected bmp280 temperature and pressure sensor. Just used for temps.

// A pointer to the dynamic created rotary encoder instance.
// This will be used in setup()
RotaryEncoder *encoder = nullptr;
int     enc_pos;
uint8_t enc_pushn_state;
int     enc_change = 0;
uint8_t enc_press = 0;
int     enc_press_debounce = 50; //msecs
bool    show_menu;
int     menu;
int     menu_line;
const uint8_t cursor = '>';
int     hs_temperature;    // stored value of heatsink temperature for the mower switch.
const char * logfile = "/log.txt";

File file;

// this is the encoder ISR. Not at all sure I want to use the encoder interrupts. Just poll in loop() for now.
//IRAM_ATTR void checkPosition()
//{
//  encoder->tick(); // just call tick() to check the state.
//}

// Going to do all my basic event timing and logging in seconds, so will use ESP32Time for convenience.
// not going to bother setting the clock, just demark time in HMS from whenever the board last got
// turned on.
ESP32Time rtc;
unsigned long last_temp_update_time;         // time last temperature was polled at, in seconds
const unsigned long temp_update_period = 10; // seconds.

unsigned long last_psu_update_time;         // time last power supply voltage and current was polled at
const unsigned long psu_update_period = 2;  // seconds.

// logfile flushes when the buffer is full.
// Manually flush via UI on termination if last fragment of log is wanted.

// create lcd object
hd44780_I2Cexp lcd;

bool espnow = true;

const uint8_t server_len = 15;
char server[server_len];
uint16_t LogPort;

//The udp library class
WiFiUDP udp;
// Use WiFiClient class to create TCP connections
WiFiClient client;

bool connected = false;

const uint8_t default_mac[] = { 0xff, 0xff, 0xff, 0xff, 0xff, 0xff };
